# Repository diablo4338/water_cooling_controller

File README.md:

# PC Water Cooling Controller

An end-to-end fan controller solution built around a custom PCB and an `ESP32-C3` controller. The repository covers the full product scope: device firmware, a desktop application for Windows and Linux, PCB manufacturing files, and the bill of materials.

The controller is designed for:
- up to 4 fans;
- up to 4 `10k` thermistors.

The desktop application works over BLE and supports pairing mode, controller connection, telemetry monitoring, and cooling parameter updates. The hardware lives in `hardware/`, and the release pipeline builds a unified set of artifacts through [`.github/workflows/release.yml`](.github/workflows/release.yml).

## Repository structure
- [`firmware/`](firmware/README.md) - `ESP-IDF` firmware for `ESP32-C3`.
- [`pcwcc/`](pcwcc/README.md) - desktop GUI for Windows and Linux.
- [`hardware/`](hardware/README.md) - KiCad project, BOM, and production exports for the PCB.
- [`tests/raspberry/`](tests/raspberry/README.md) - Raspberry Pi helper for hardware integration tests.
- [`docker/`](docker/README.md) - local Docker environment for release-build verification.
- [`docs/`](docs/) - additional notes on architecture, CLI, release flow, and hardware.

## Release artifacts
The `scripts/make_release.sh` script and the `Release` workflow produce:
- firmware for `ESP32-C3`;
- a Linux `AppImage` for the desktop client;
- a production archive with `Gerber` and `drill` files for PCB manufacturing;
- checksums;
- the BOM is stored separately in [`hardware/production/bom/main.csv`](hardware/production/bom/main.csv).

Build details and structure notes are kept in the `README` files of the corresponding directories.

## License

This project is licensed for non-commercial use only.

Commercial use is not permitted without prior written permission from the author.

See [LICENSE](LICENSE) for details.

## Safety disclaimer

This is an experimental DIY hardware/software project. Use it at your own risk.
Incorrect wiring, firmware, configuration, or installation may cause hardware
damage, overheating, fire, or injury.

See [DISCLAIMER.md](DISCLAIMER.md).

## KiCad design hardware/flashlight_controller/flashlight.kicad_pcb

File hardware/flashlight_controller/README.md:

# Flashlight controller — revision 0.2

Рабочий проект: `flashlight.kicad_pro`, схема `flashlight.kicad_sch`, плата
`flashlight.kicad_pcb`. Исходная версия сохранена в
`revision_backup_20260924.zip`. Монтаж снизу, питание 2S 6–8,4 В,
лампа около 1 А. Генераторы находятся в `tools/`.

## Повторное использование компонентов

Референс: `U:/plate_schemas/speed_and_temp_v8`, все восемь переданных файлов
доступны. Перечень компонентов всех листов сохранён в `tools/reference_parts.json`.
Скопированные посадочные места автономны: для повторной сборки проекта диск U:
не нужен.

| Здесь | Референс | Решение |
|---|---|---|
| U1 | esp U1 | Тот же ESP32-C3-WROOM-02 |
| U2 | fan_power U5 | Тот же MCP16331T-E/CH |
| U3 | power U2 | TPS7A02-3.3 (TPS7A0233PDBVR), SOT-23-5, как в референсе |
| C10, C11 | power C6, C5 | 1 мкФ на входе и 4,7 мкФ на выходе LDO, 0805 |
| U4 | ina U6 | Тот же INA226, корпус 3×3 мм с шагом 0,5 мм |
| Q1 | fan_power Q1 | MMFTP3334K вместо AO3401A, G1/S2/D3 |
| Q2 | fan_power Q2, esp Q3 | NXV40UNR вместо 2N7002, G1/S2/D3 |
| R1 | ina R17 | WSL2512R0470FEA, 47 мОм / 1% / 1 Вт |
| D1 | fan_power D2 | PD3S120LQ, скопировано посадочное место PowerDI323 |
| D2 | fan_power D3 | 1N4148WS-HG3_A-08 |
| SW1, SW2 | esp SW1–SW3 | Скопировано посадочное место кнопок |
| R2, R8 | fan_power R29, R34 | 61,9 кОм и 100 кОм из референса |
| R3–R6, R9–R16, R18 | разные листы | Повторно используются номиналы 1 кОм, 100 кОм, 10 Ом, 10 кОм, 4,7 кОм |
| C2–C7, C10, C12–C16 | разные листы | 100 нФ, 1 мкФ и 10 мкФ в 0805; напряжение и диэлектрик по BOM |

Новые номиналы: R7 523 кОм, R17 12,4 кОм. Сохранены конденсаторы 22 мкФ,
470 мкФ и дроссель 22 мкГн: они выбраны для этого источника и нагрузки.
SRN4018-100M из референса имеет 10 мкГн; без проверки устойчивости и пульсаций
его не подставляем вместо рекомендованных для 5 В 22 мкГн.
Установлен TPS7A02-3.3 из референса: IN и EN подключены к 5 В, NC оставлен
неподключённым. Его номинальный выходной ток — 200 мА; работу ESP32-C3 с радио
нужно проверить на прототипе по просадке 3,3 В. ADS1115 не требуется для
одного термодатчика. Разъёмы SATA и вентиляторов не соответствуют назначению платы.

## Делители и потребление

R7/R8: **523 кОм / 100 кОм**, вместо 52,3 кОм / 10 кОм.
При VFB = 0,8 В выход 4,984 В, ток делителя 8 мкА вместо 80 мкА.
При типичном токе входа FB 3 нА добавочная ошибка выхода около 1,57 мВ.
Максимальный ток FB производитель не гарантирует, поэтому 100 кОм снизу —
выбранный инженерный предел, а не паспортный максимум. Увеличение ещё на порядок
без измерений неоправданно. Для 1% резисторов и диапазона VFB 0,784–0,816 В
статический диапазон примерно 4,803–5,170 В без учёта входного тока FB.
На прототипе проверить запуск, пульсации и скачки нагрузки при 6 и 8,4 В.

R2 = 61,9 кОм снижает постоянный ток включённого ключа примерно до
95–134 мкА. Увеличение до мегомов ограничено утечкой защищённого затвора
MMFTP3334K: 10 мкА плюс утечка Q2 1 мкА дали бы 0,681 В на 61,9 кОм.
Это оценка по указанным в паспортах условиям, не гарантия при любой температуре.
Ключ предназначен для медленного включения/выключения лампы; высокочастотный PWM
с резистивным выключением затвора не проверен.

Напряжение аккумулятора измеряет VBUS INA226 непосредственно; отдельного
постоянно включённого делителя батареи нет. Шунт 47 мОм даёт 47 мВ и 47 мВт
при 1 А. Диапазон INA226 ±81,92 мВ соответствует ±1,743 А **общего** тока,
включая электронику; выше этого измерение насыщается.
Для Current_LSB = 100 мкА регистр CAL = round(0,00512 / (0,0001 × 0,047)) = 1089.
Прошивку с прежними 20 мОм использовать без изменения калибровки нельзя.

Экономия на делителях не означает микроамперного сна всей платы:
включённый MCP16331 сам потребляет типично около 1 мА. INA226 также следует
переводить в power-down между измерениями, если требуется экономичный режим.

## АЦП и термодатчик

**Предварительное допущение: NTC 10 кОм при 25 °C, B3950, диапазон 0…100 °C.**
Фактический датчик и его допуски ещё нужно подтвердить. Выбранный номинал R17
нельзя считать окончательным для неизвестного датчика или отрицательных температур.

Используется GPIO0 / ADC1_CH0. GPIO1 / TEMP_EXCITE питает делитель только
на время измерения. R17 = 12,4 кОм; R18 = 1 кОм; C16 = 100 нФ у входа АЦП.
Постоянное питание 3,3 В с R17 убрано. Большое сопротивление R17 при том же NTC
ухудшило бы полезный размах сигнала; выключаемое питание уменьшает средний ток
без этого ухудшения.

| Температура | Сопротивление NTC, примерно | Напряжение АЦП при 3,3 В |
|---|---|---|
| 0 °C | 33,62 кОм | 2,411 В |
| 25 °C | 10 кОм | 1,473 В |
| 100 °C | 697,5 Ом | 0,176 В |

Размах 2,235 В использует около 89% диапазона 0…2,5 В.
Верхняя точка оставляет запас до насыщения, но после получения допусков датчика
нужен окончательный worst-case расчёт. При обрыве NTC вход поднимается к 3,3 В:
это насыщение измерителя; прошивка должна считать такой результат неисправностью,
а не температурой. При коротком замыкании вход близок к нулю.

Последовательность будущей прошивки:

1. Настроить ADC1_CH0 на ATTEN3 (`ADC_ATTEN_DB_12`; старое имя `ADC_ATTEN_DB_11`),
   включить поддерживаемую ESP-IDF калибровку.
2. Установить GPIO1 в высокий уровень; подождать **15 мс**.
   Даже при обрыве постоянная времени (12,4 кОм + 1 кОм) × 100 нФ = 1,34 мс.
3. Отбросить первую выборку, усреднить несколько измерений, перевести результат
   в мВ через калибровочный API. Измерения редкие, не поток 100 квыб/с.
4. Установить GPIO1 в низкий уровень до следующего измерения, в том числе перед сном.
5. Рассчитать Rntc = 12400 × Vadc / (Vexcite − Vadc), затем
   T = 1 / (1/298,15 + ln(Rntc/10000)/3950) − 273,15.
   Использовать измеренное/откалиброванное Vexcite: напряжение GPIO не идеальные 3,3 В.

Ток при 25 °C во время измерения около 147 мкА. При включении на 20 мс раз
в секунду среднее потребление делителя около 2,95 мкА; токи утечки сюда не включены.
Для C16 100 нФ обеспечен локальный запас заряда SAR и фильтрация; буфер для этой
редкой выборки не установлен. Итоговую погрешность проверить на известных
сопротивлениях с фактической частотой выборки и работающим радио. 12 бит не означают
12 бит абсолютной точности: для ATTEN3 паспортная ошибка после калибровки ±35 мВ
при оговорённых условиях, что особенно заметно на горячем конце NTC.

## Плата и проверки

В генераторе убраны отверстия в центральном паде ESP32. Трассировщик запрещает
via на любых падах, включая площадки той же цепи. Минимальный зазор между краем
кольца via и прямоугольником, охватывающим медь пада, — 0,15 мм.
`tools/verify_design.py` проверяет геометрию итогового файла, включая тепловые via,
и соответствие экспортированного netlist спецификации соединений.
Отчёты: `erc.rpt`, `drc.json`, `verification.json`.

Для генерации запустить `tools/build_project.py`, `tools/route_board.py`,
`tools/finish_board.py`, затем KiCad CLI ERC, DRC с `--refill-zones --save-board`,
экспорт XML netlist и `tools/verify_design.py`. Использовать настроенный Python SDK.
`tools/import_reference.py` нужен только для повторного импорта оригиналов.

## Документация производителей

- [ESP32-C3 datasheet, ADC и потребление](https://documentation.espressif.com/ESP32-C3_Datasheet_en.pdf)
- [Espressif: схема и вход АЦП](https://docs.espressif.com/projects/esp-hardware-design-guidelines/en/latest/esp32c3/schematic-checklist.html)
- [ESP-IDF: ADC](https://docs.espressif.com/projects/esp-idf/en/latest/esp32c3/api-reference/peripherals/adc/index.html)
- [MCP16331, раздел 5.2 и характеристики](https://ww1.microchip.com/downloads/en/DeviceDoc/MCP16331-Data-Sheet-20005308.pdf)
- [MMFTP3334K](https://diotec.com/files/diotec/productfiles/datasheet/mmftp3334k.pdf)
- [NXV40UN](https://assets.nexperia.com/documents/data-sheet/NXV40UN.pdf)
- [PD3S120LQ](https://www.diodes.com/datasheet/download/PD3S120LQ.pdf)
- [TPS7A02](https://www.ti.com/product/TPS7A02)
- [SRN4018](https://www.bourns.com/docs/product-datasheets/srn4018.pdf)
- [INA226](https://www.ti.com/lit/ds/symlink/ina226.pdf)

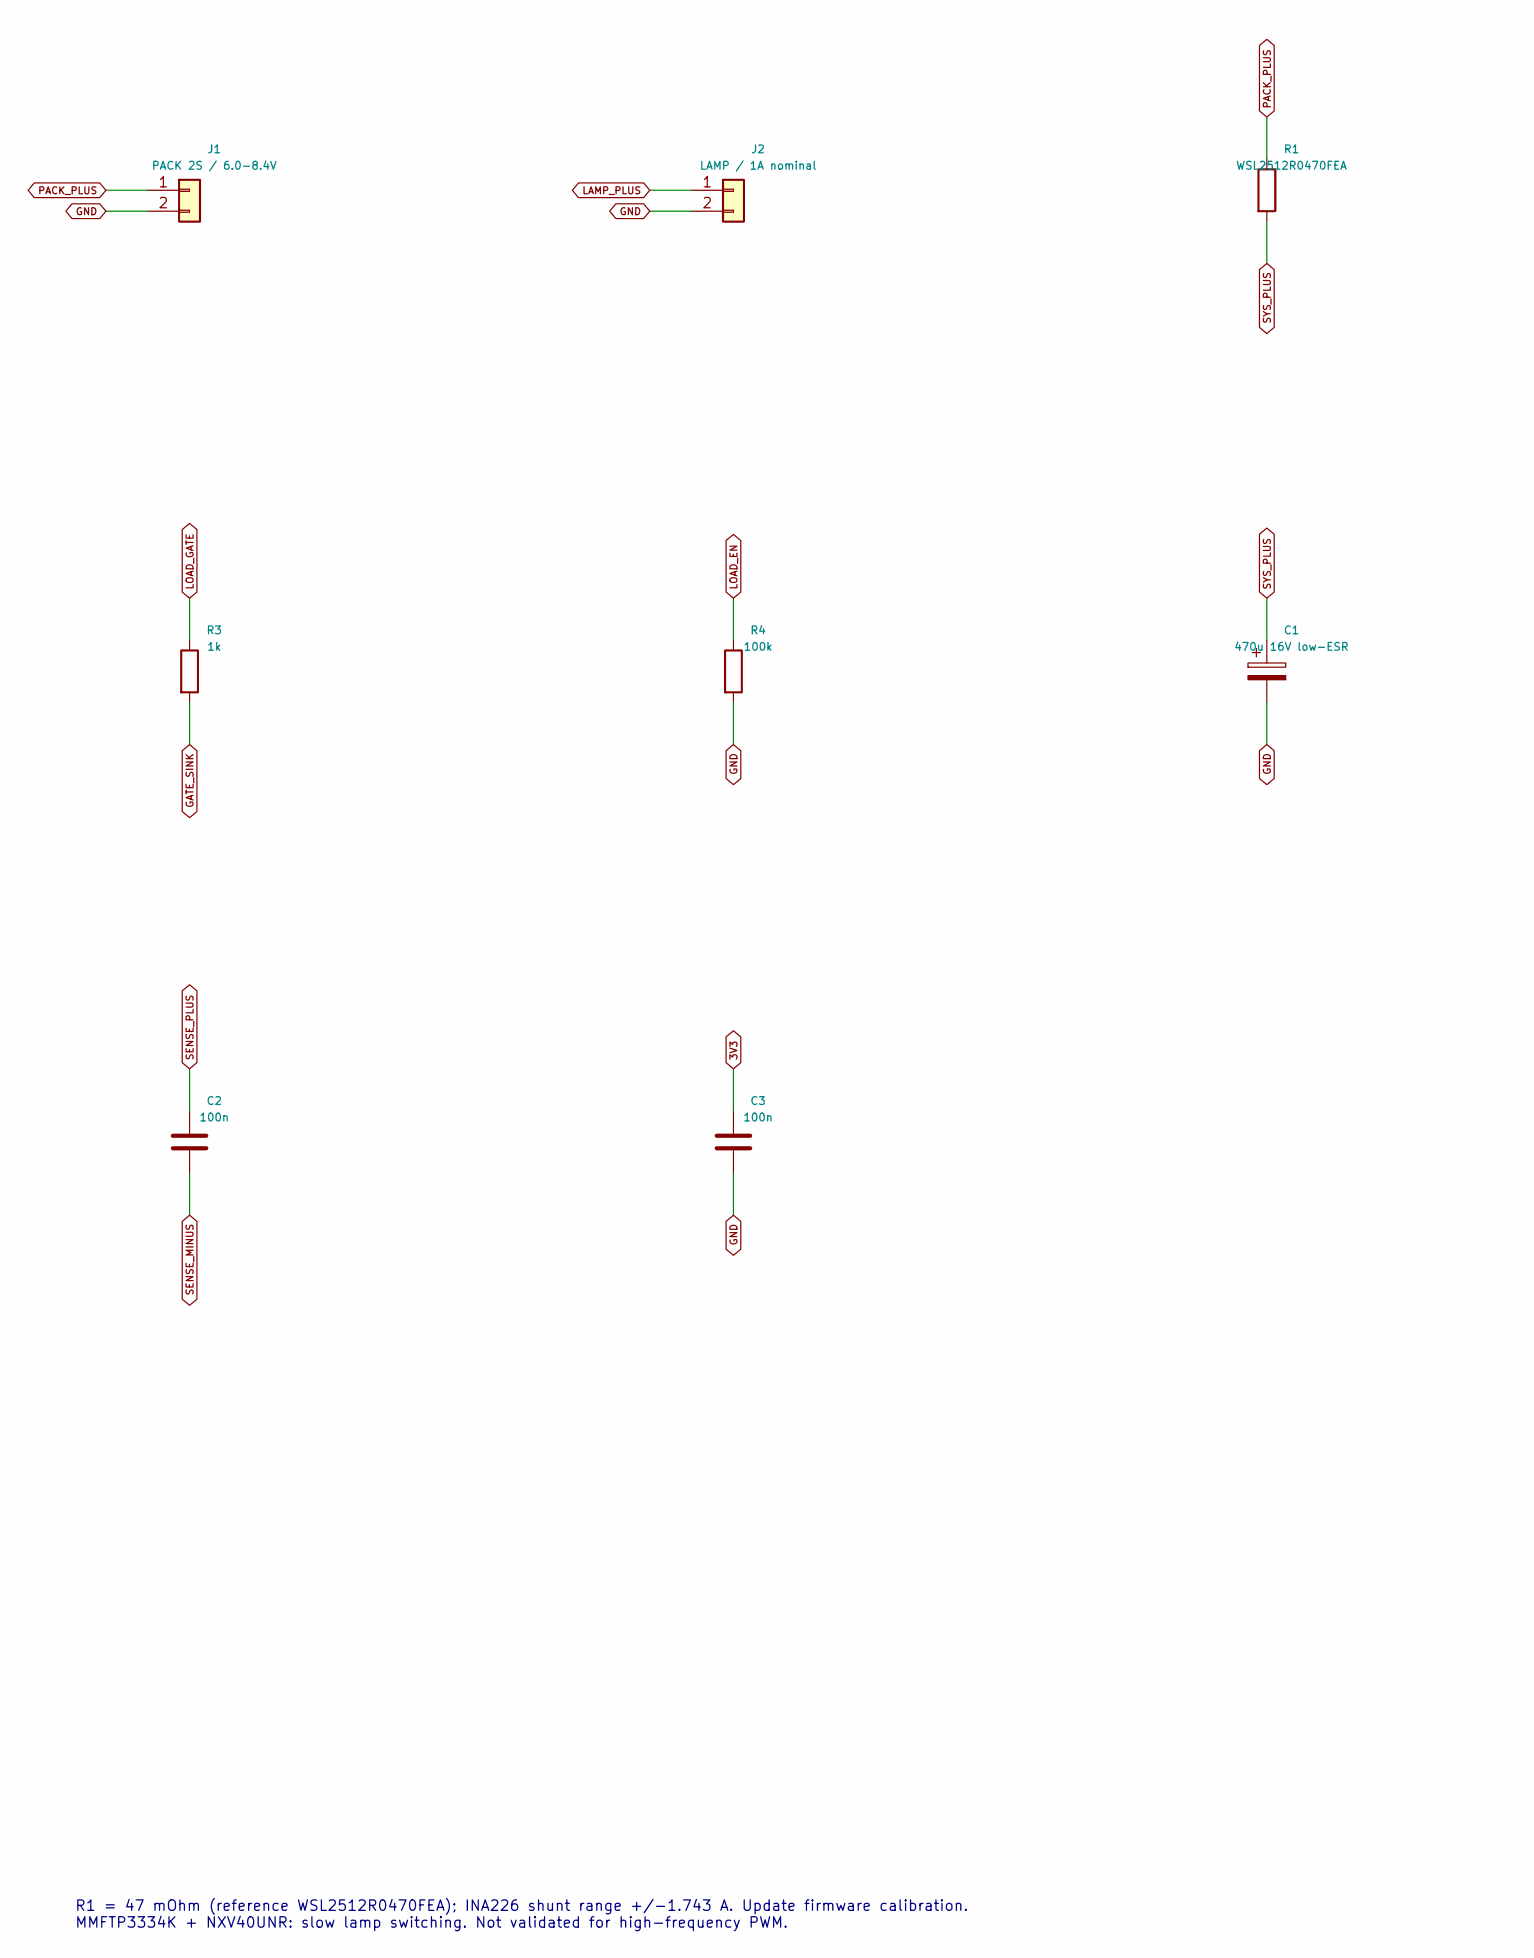
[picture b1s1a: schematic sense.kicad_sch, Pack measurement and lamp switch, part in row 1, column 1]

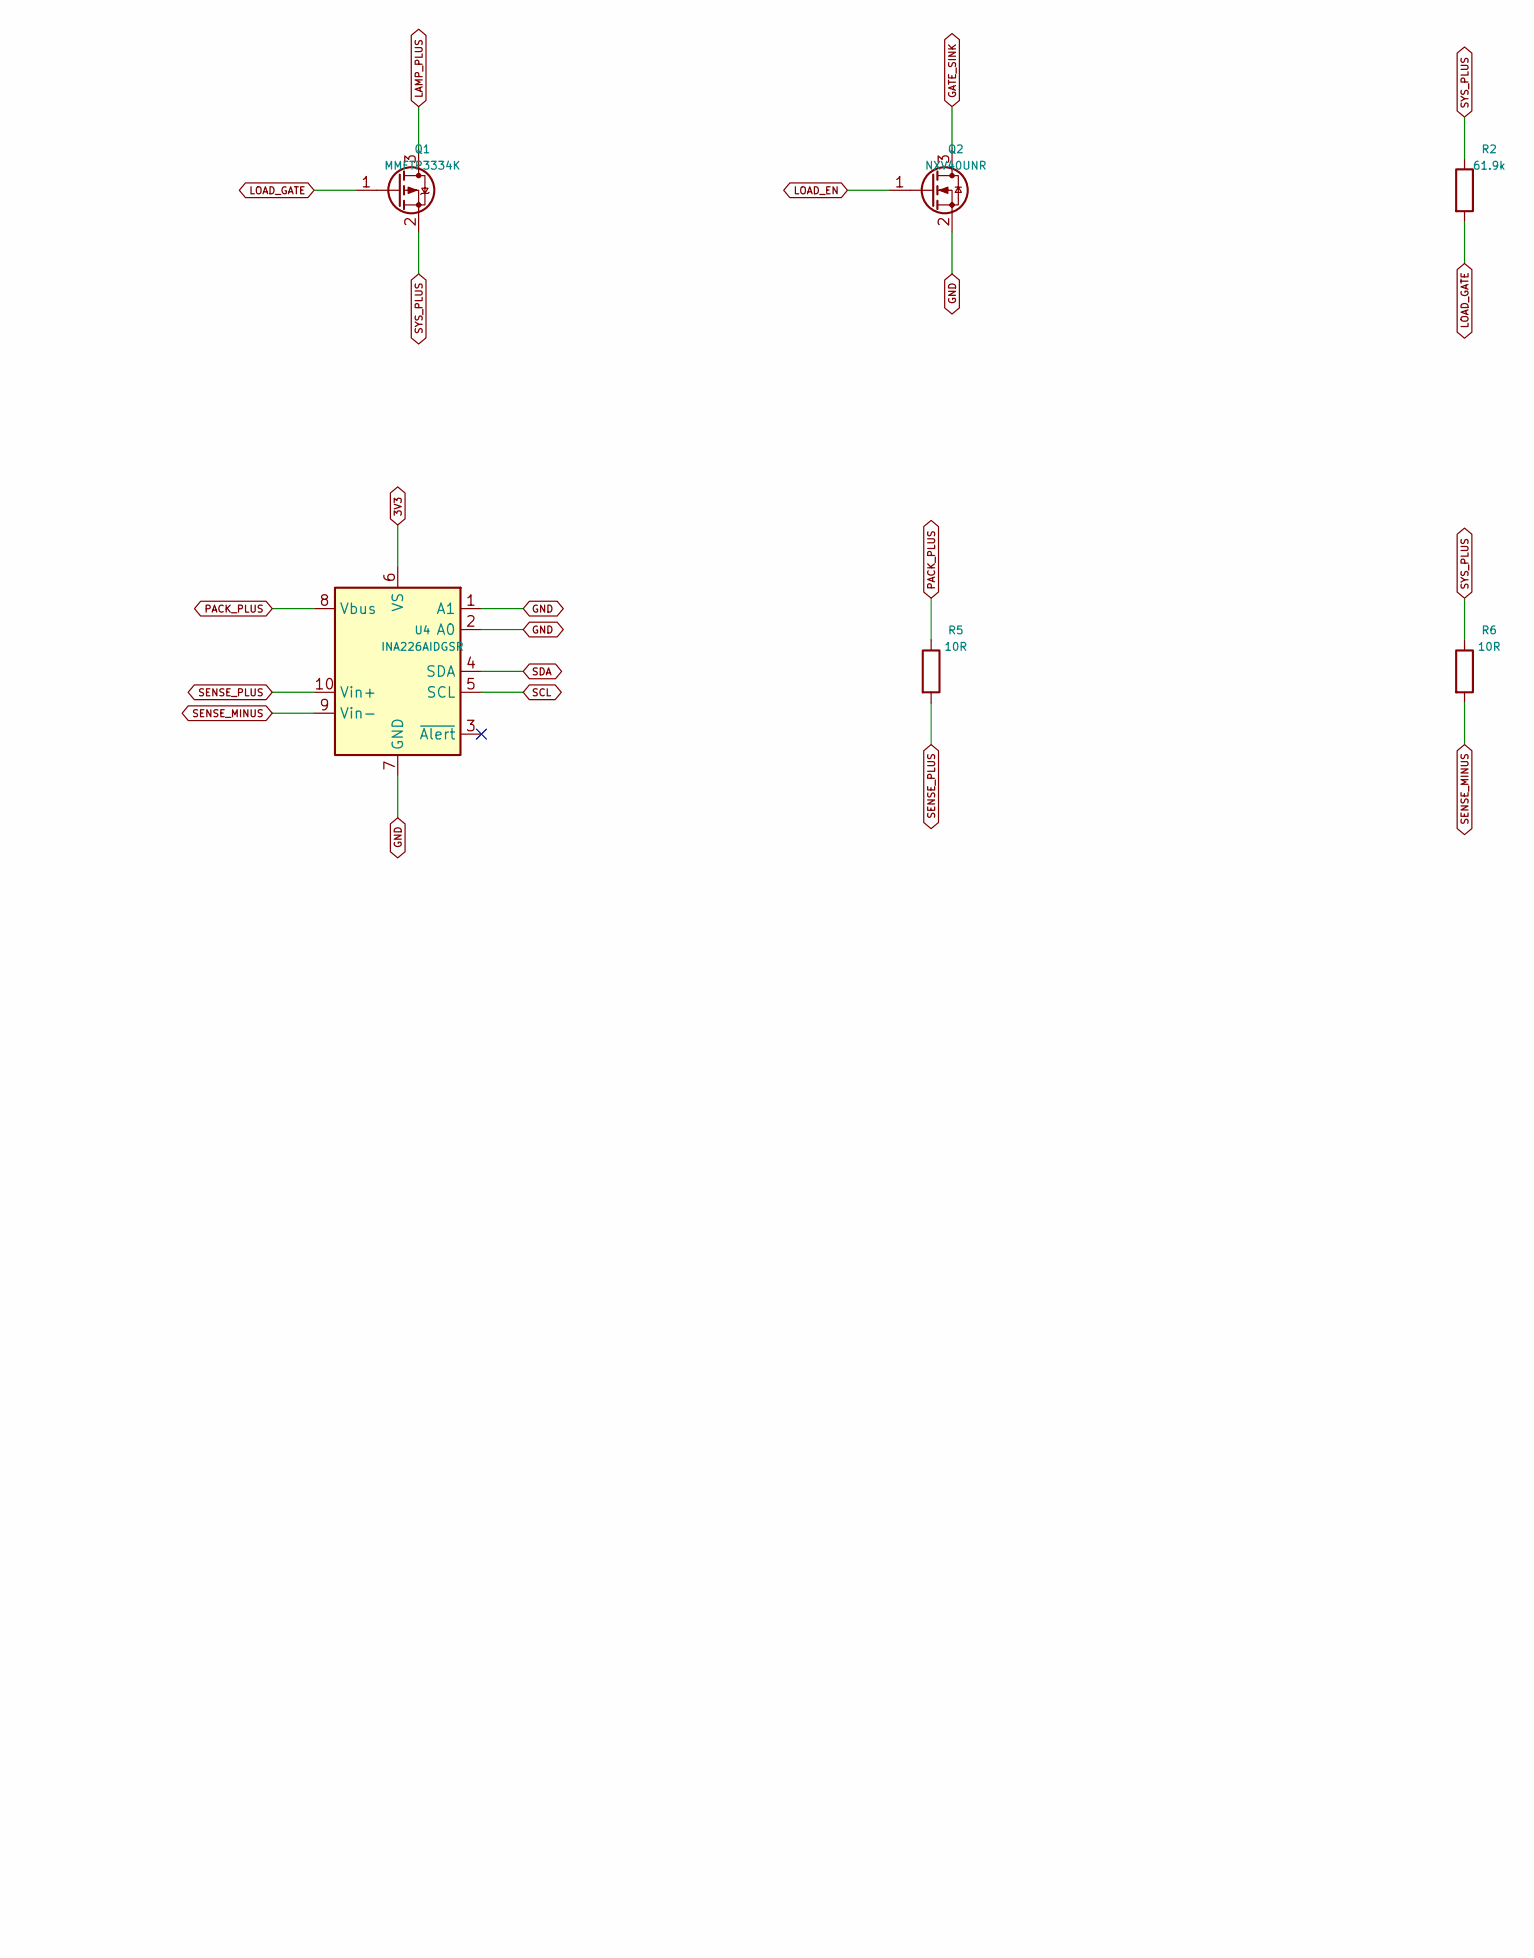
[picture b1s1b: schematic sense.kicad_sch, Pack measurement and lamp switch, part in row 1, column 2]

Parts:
C1: 470u 16V low-ESR; Electrolytic_D10_P5
C2, C3: 100n; C_0805_2012Metric
J1: PACK 2S / 6.0-8.4V; WirePads_2x_5mm
J2: LAMP / 1A nominal; WirePads_2x_5mm
Q1: MMFTP3334K; SOT-23
Q2: NXV40UNR; SOT-23
R1: WSL2512R0470FEA; R_2512_6332Metric
R2: 61.9k; R_0805_2012Metric
R3: 1k; R_0805_2012Metric
R4: 100k; R_0805_2012Metric
R5, R6: 10R; R_0805_2012Metric
U4: INA226AIDGSR; MSOP-10_3x3mm_P0.5mm

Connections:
3V3: C3.1, U4.6 (VS); also elsewhere on the board
GATE_SINK: Q2.3 (D), R3.2
GND: C1.2, C3.2, J1.2, J2.2, Q2.2 (S), R4.2, U4.1 (A1), U4.2 (A0), U4.7 (GND); also elsewhere on the board
LAMP_PLUS: J2.1, Q1.3 (D)
LOAD_EN: Q2.1 (G), R4.1; also elsewhere on the board
LOAD_GATE: Q1.1 (G), R2.2, R3.1
PACK_PLUS: J1.1, R1.1, R5.1, U4.8 (Vbus)
SCL: U4.5 (SCL); also elsewhere on the board
SDA: U4.4 (SDA); also elsewhere on the board
SENSE_MINUS: C2.2, R6.2, U4.9 (Vin-)
SENSE_PLUS: C2.1, R5.2, U4.10 (Vin+)
SYS_PLUS: C1.1, Q1.2 (S), R1.2, R2.1, R6.1; also elsewhere on the board

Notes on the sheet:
R1 = 47 mOhm (reference WSL2512R0470FEA); INA226 shunt range +/-1.743 A. Update firmware calibration. MMFTP3334K + NXV40UNR: slow lamp switching. Not validated for high-frequency PWM.

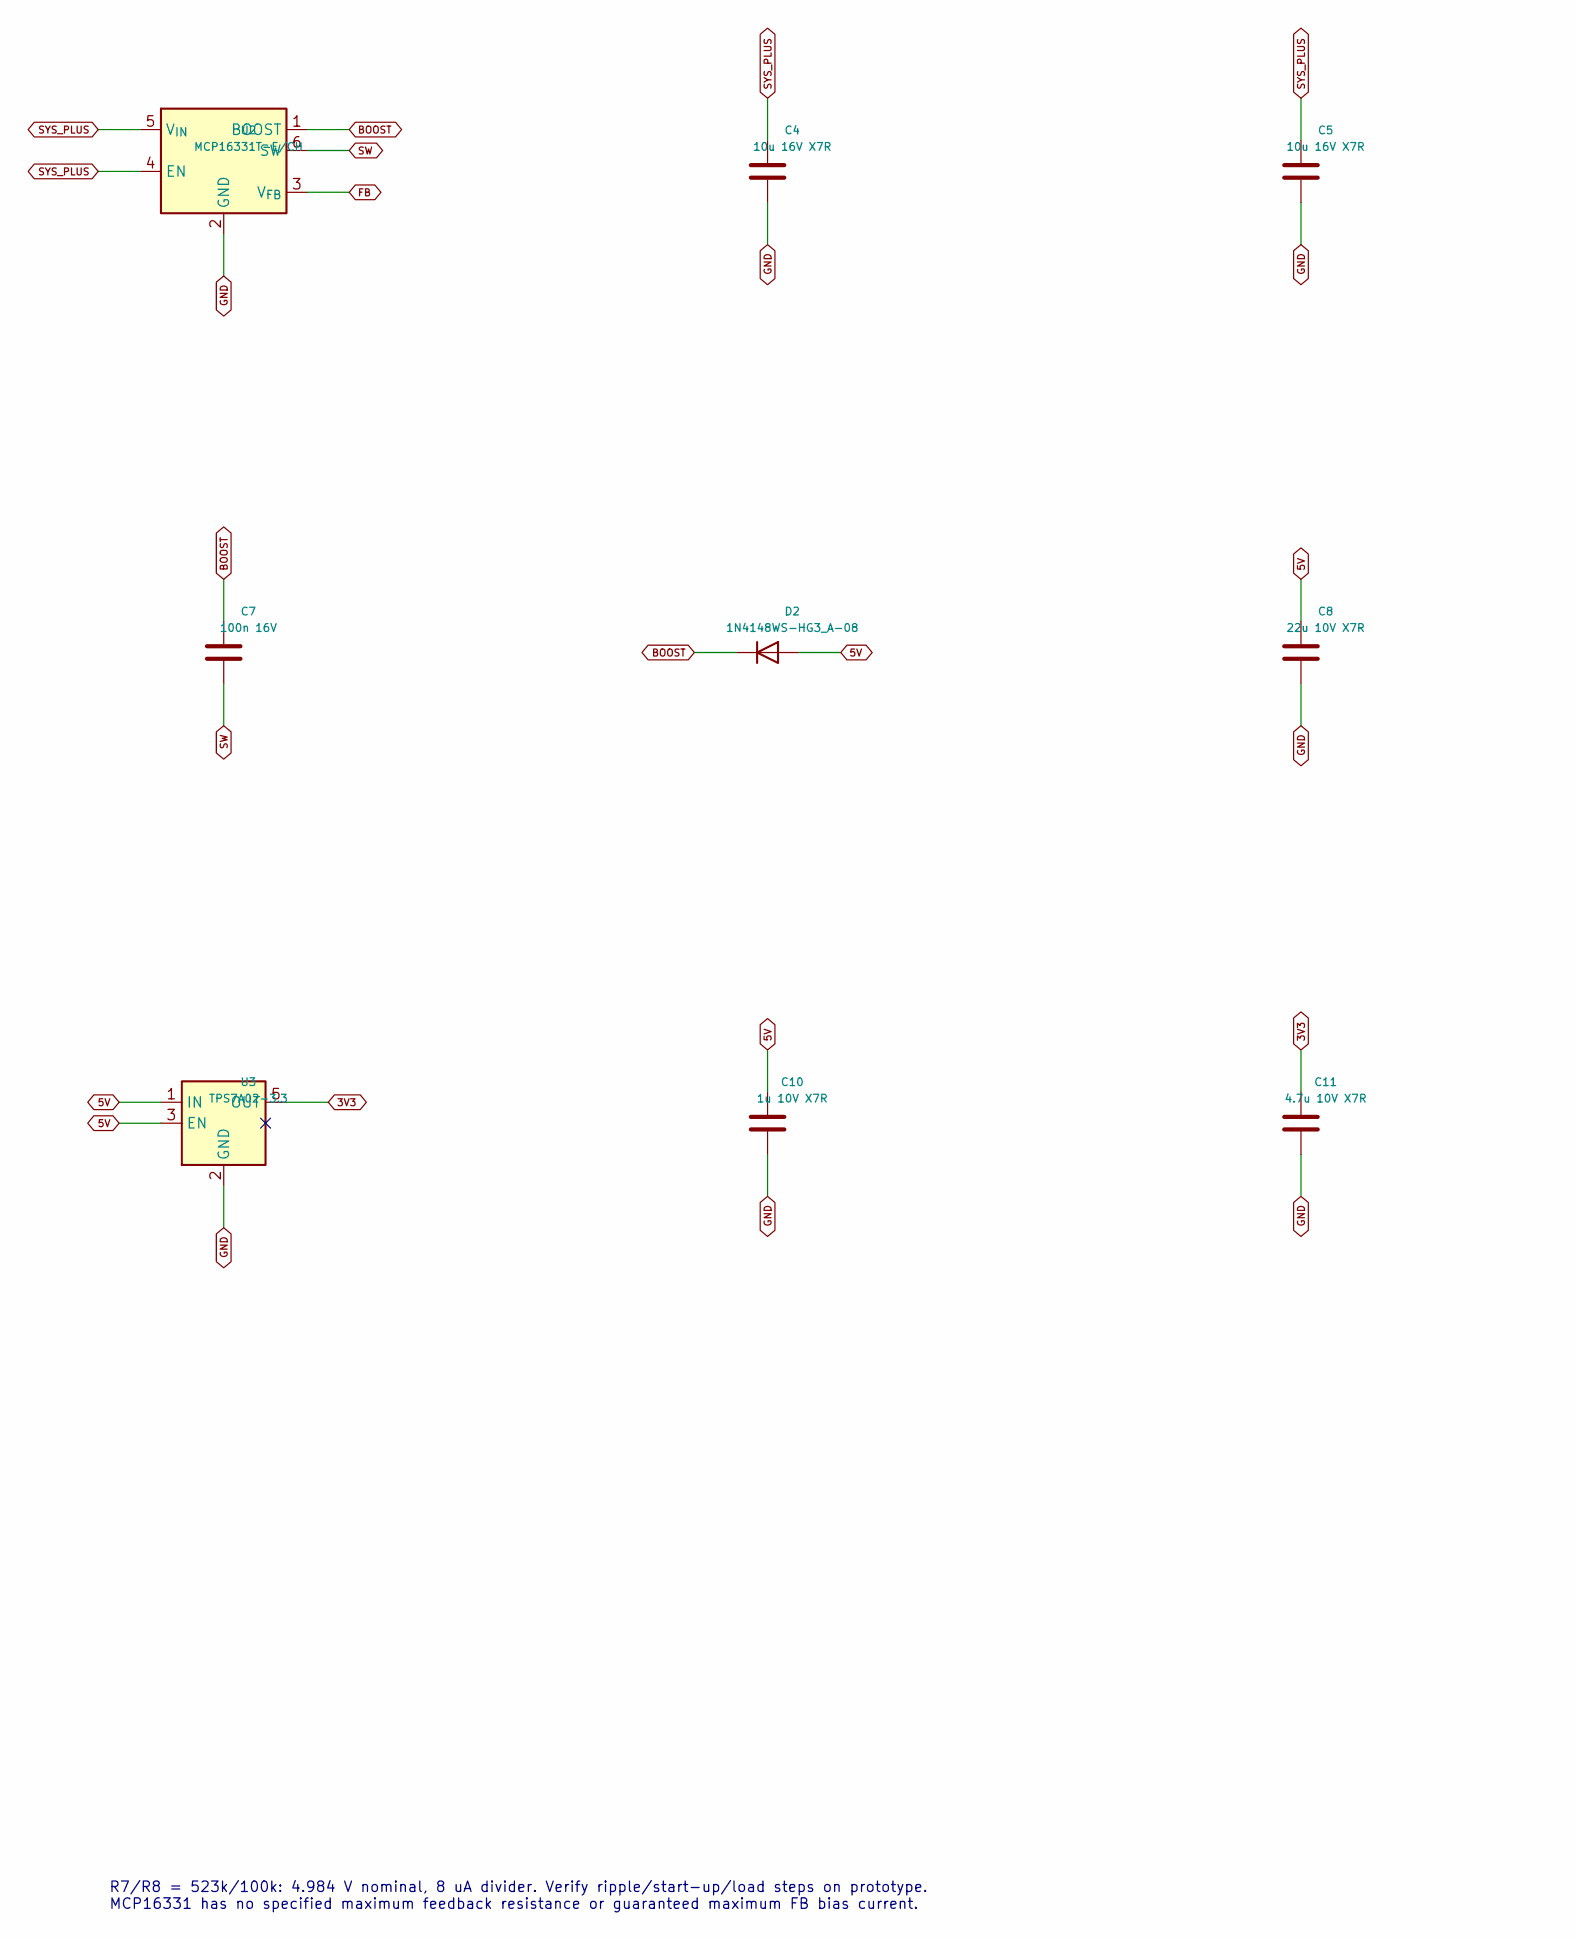
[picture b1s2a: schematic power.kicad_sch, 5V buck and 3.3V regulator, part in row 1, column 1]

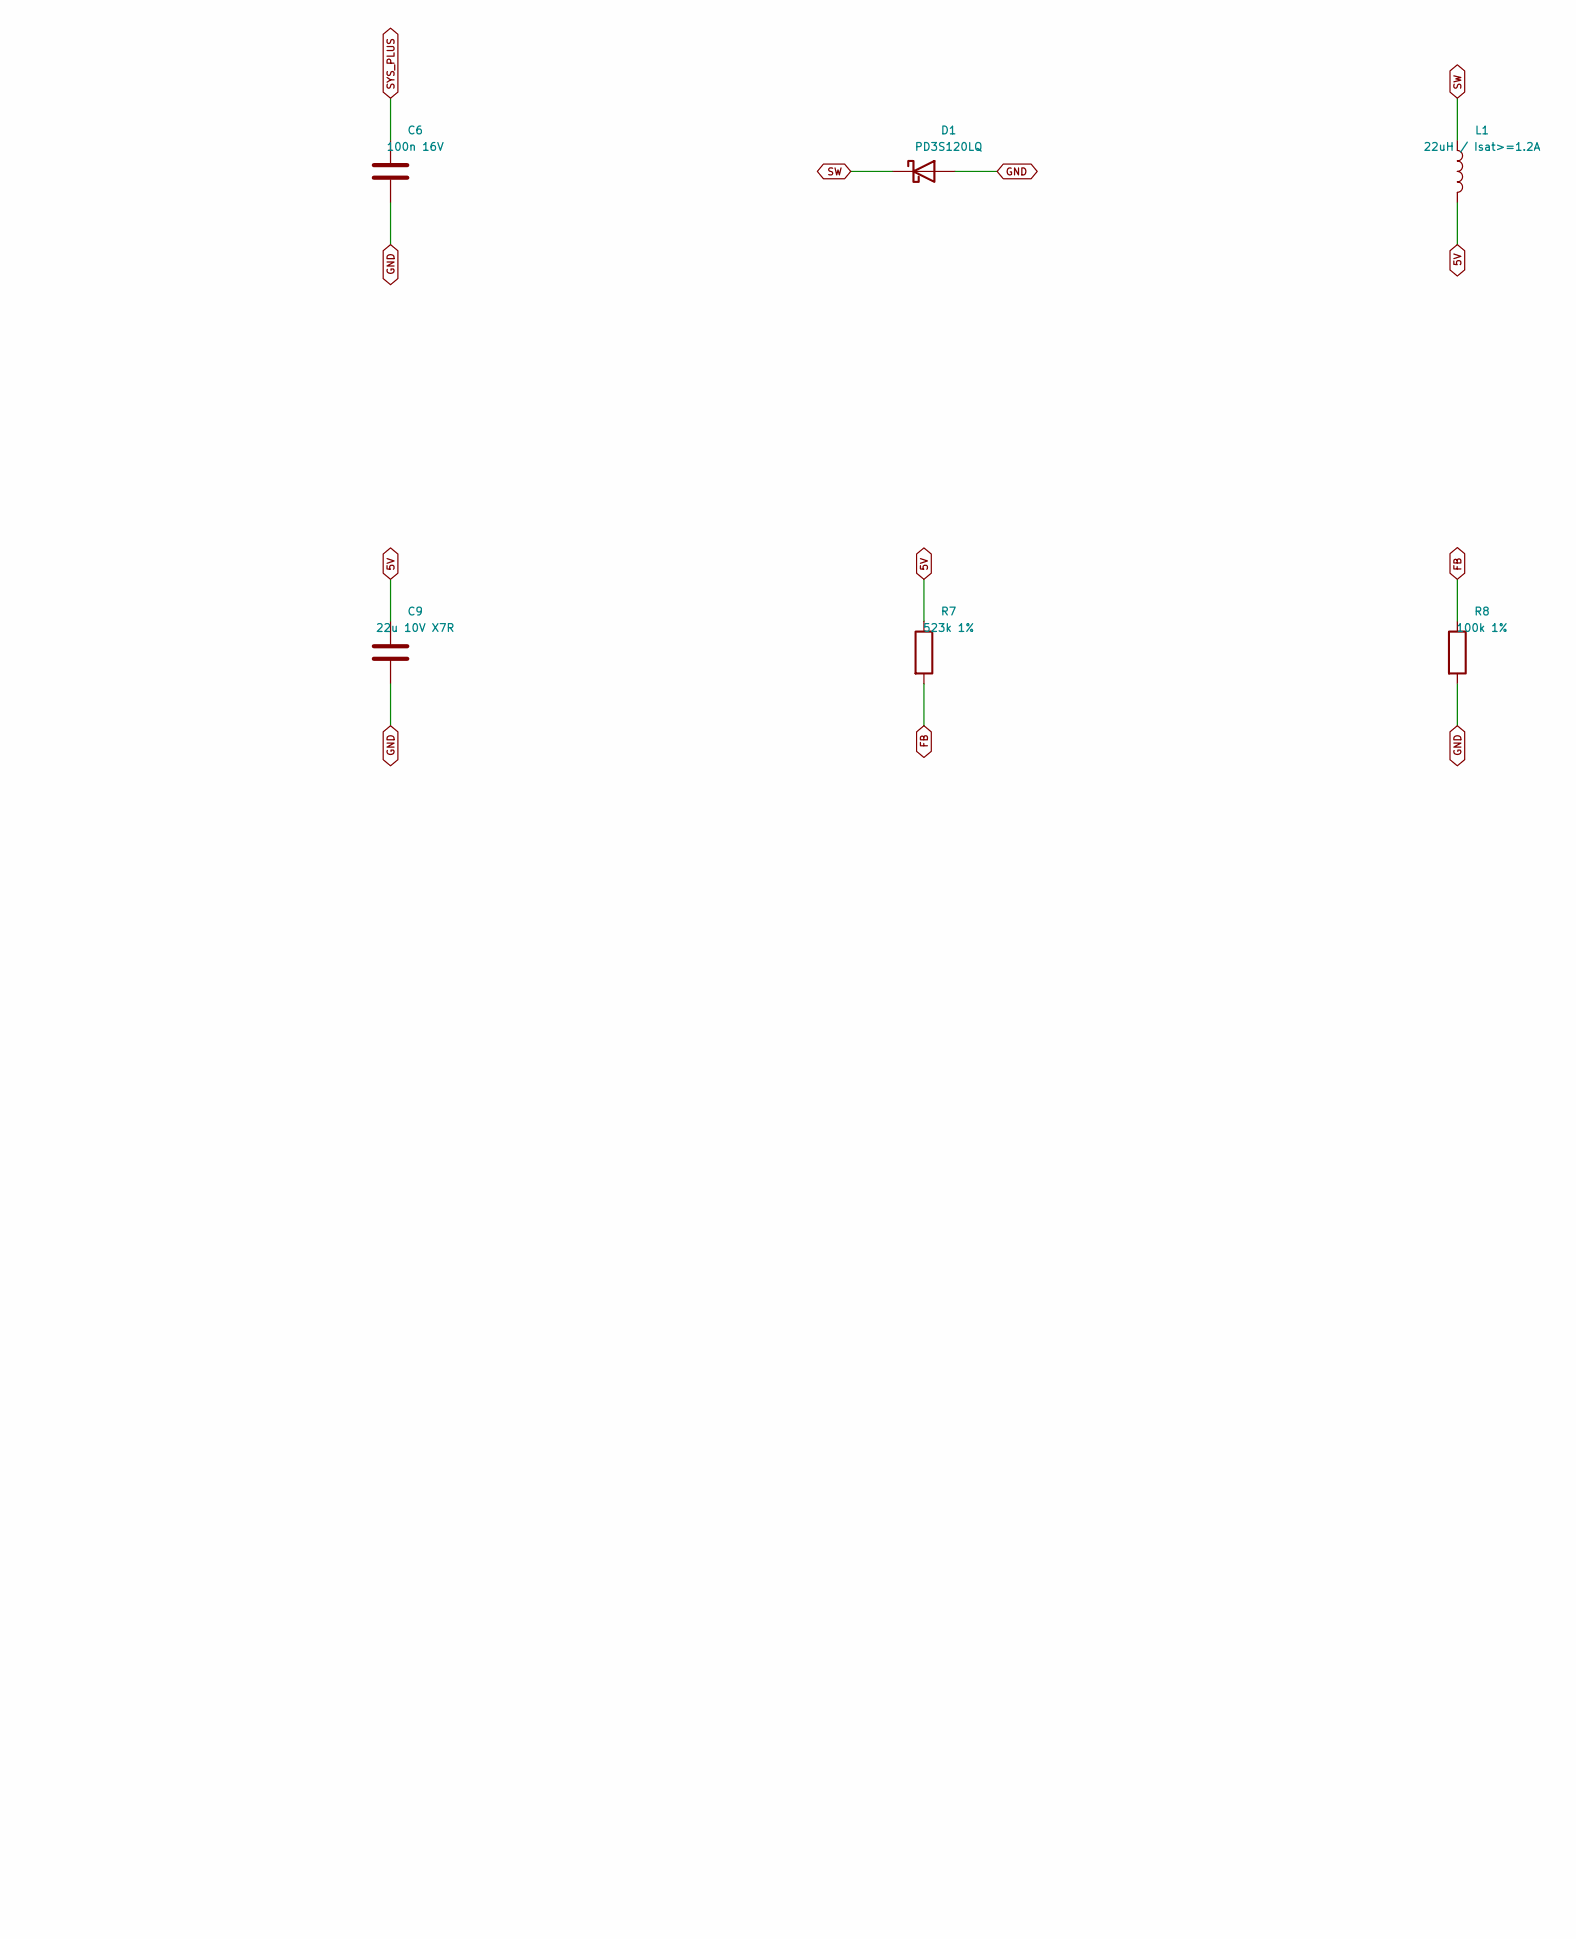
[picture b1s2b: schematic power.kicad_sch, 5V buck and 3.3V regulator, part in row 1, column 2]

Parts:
C4, C5: 10u 16V X7R; C_0805_2012Metric
C6, C7: 100n 16V; C_0805_2012Metric
C8, C9: 22u 10V X7R; C_1206_3216Metric
C10: 1u 10V X7R; C_0805_2012Metric
C11: 4.7u 10V X7R; C_0805_2012Metric
D1: PD3S120LQ; Reference_PowerDI323
D2: 1N4148WS-HG3_A-08; D_SOD-323
L1: 22uH / Isat>=1.2A; L_Bourns_SRN6045TA
R7: 523k 1%; R_0805_2012Metric
R8: 100k 1%; R_0805_2012Metric
U2: MCP16331T-E/CH; SOT-23-6
U3: TPS7A02-3.3; SOT-23-5

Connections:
3V3: C11.1, U3.5 (OUT); also elsewhere on the board
5V: C8.1, C9.1, C10.1, D2.2 (A), L1.2, R7.1, U3.1 (IN), U3.3 (EN)
BOOST: C7.1, D2.1 (K), U2.1 (BOOST)
FB: R7.2, R8.1, U2.3 (V_{FB})
GND: C4.2, C5.2, C6.2, C8.2, C9.2, C10.2, C11.2, D1.2 (A), R8.2, U2.2 (GND), U3.2 (GND); also elsewhere on the board
SW: C7.2, D1.1 (K), L1.1, U2.6 (SW)
SYS_PLUS: C4.1, C5.1, C6.1, U2.4 (EN), U2.5 (V_{IN}); also elsewhere on the board

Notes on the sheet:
R7/R8 = 523k/100k: 4.984 V nominal, 8 uA divider. Verify ripple/start-up/load steps on prototype. MCP16331 has no specified maximum feedback resistance or guaranteed maximum FB bias current.
